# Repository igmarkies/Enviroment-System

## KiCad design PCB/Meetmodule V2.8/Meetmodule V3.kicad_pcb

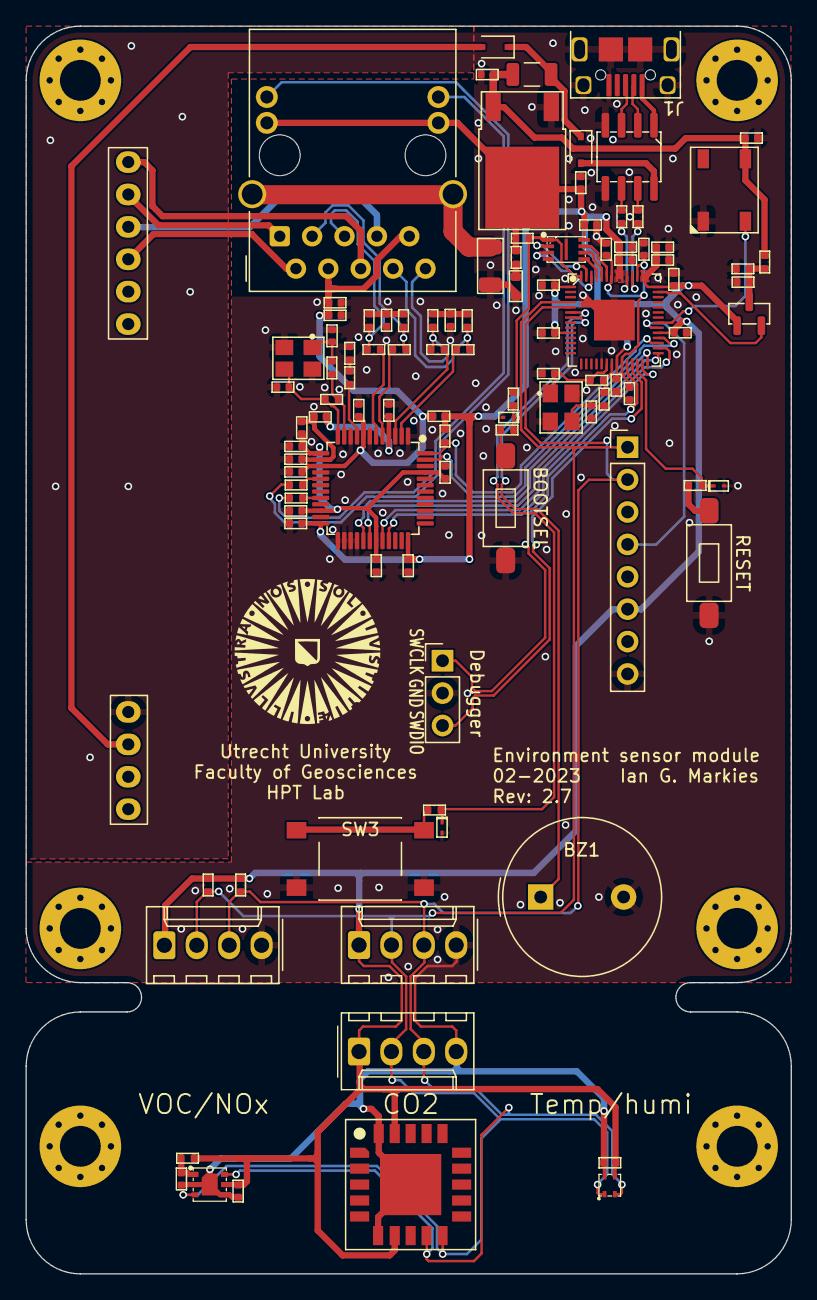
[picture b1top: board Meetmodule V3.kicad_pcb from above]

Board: 2 copper layers, 60.0 x 97.8 mm, 103 parts (0 on the bottom side), 74 nets.

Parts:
BZ1: Buzzer; Buzzer_TDK_PS1240P02BT_D12.2mm_H6.5mm
C1, C2, C3, C4, C5, C6, C7, C8, C9, C15, C18, C19, C20, C21, C22, C23, C25, C26, C27, C28, C29, C30, C32, C36, C39: 0.1uF; Cap 0402_1005Metric
C10, C11: 10uF; Cap 0402_1005Metric
C12, C13, C14, C24, C31, C37, C38: 1uF; Cap 0402_1005Metric
C16, C17: 15pF; Cap 0402_1005Metric
C33: 1nF/2kV; C_1206_3216Metric
C34, C35: 18pF; Cap 0402_1005Metric
D1, D2: BAT60A; D_SOD-323
D3: LED
D4, D6, D7: ESD9B3.3ST5G; D_SOD-923
D5: WS2812B; LED_WS2812B_PLCC4_5.0x5.0mm_P3.2mm
F1: Fuse; Fuse_1206_3216Metric
FB1, FB2, FB3: 120r@100MHz; L_0402_1005Metric
J1: USB_B_Micro; Micro USB, Type B
J2: Ethernet_(100_Base-T_&_PoE); PoE, 10 Pin with LED
J3: Display; PinHeader_1x08_P2.54mm_Vertical
J4: Extra I2C; Molex_KK-254_AE-6410-04A_1x04_P2.54mm_Vertical
J5: Debugger; PinHeader_1x03_P2.54mm_Vertical
J6: Breakout 1; Molex_KK-254_AE-6410-04A_1x04_P2.54mm_Vertical
J7: Breakout 2; Molex_KK-254_AE-6410-04A_1x04_P2.54mm_Vertical
MOD1: Adafruit_3847_connector; Adafruit 3847 connector
Q1: 2N7002; SOT-23
R1, R21, R22: 470R; Res 0402_1005Metric
R2, R3, R8, R10: DNP; Res 0402_1005Metric
R4, R5: 27R; Res 0402_1005Metric
R6: 200k; Res 0402_1005Metric
R7: 100k; Res 0402_1005Metric
R9, R11: 1k; Res 0402_1005Metric
R12: 4k7; Res 0402_1005Metric
R13, R14, R15, R16: 49R9; Res 0402_1005Metric
R17, R18, R19, R20: 3R3; Res 0402_1005Metric
R23: 12K/1%; Res 0402_1005Metric
R24: 300R/1%; Res 0402_1005Metric
R25: 1M; Res 0402_1005Metric
R26: 0R; Res 0402_1005Metric
R27: 4R7; Res 0402_1005Metric
R28, R29, R30: 100R; Res 0402_1005Metric
SW1: BOOTSEL; Switch
SW2: RESET; Switch
SW3: Display; SW_Push_1P1T_NO_6x6mm_H9.5mm
U1: NCP1117-3.3_TO252; TO-252-2
U2: USB6B1; SOIC-8_3.9x4.9mm_P1.27mm
U3: RP2040; QFN-56-1EP_7x7mm_P0.4mm_EP3.2x3.2mm
U4: W25Q16JVUXIQ; SON50P300X200X60-9N
U5: W5100S; LQFP48
U6: SCD4x; SDC4x
U7: SGP41; XDCR_SGP41-D-R4
U8: SHT4x; XDCR_SHT41-AD1B-R2
Y1: 12MHz; Crystal_SMD_Abracon_ABM8G-4Pin_3.2x2.5mm
Y2: 25MHz; Crystal_SMD_Abracon_ABM8G-4Pin_3.2x2.5mm

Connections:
+1V1: C1.1, C2.1, C12.1, U3.23 (DVDD), U3.45 (VREG_VOUT), U3.50 (DVDD)
+1V2A: C23.1, FB2.1, U5.4 (1V2A)
+1V2D: C25.1, C26.1, C27.1, C28.1, FB3.2, U5.13 (1V2D), U5.22 (1V2D), U5.31 (1V2D), U5.45 (1V2D)
+1V2O: C24.1, FB2.2, FB3.1, U5.14 (1V2O)
+3.3V: C3.1, C4.1, C5.1, C6.1, C7.1, C8.1, C9.1, C11.1, C13.1, C14.1, C18.1, C19.1, C20.1, C36.2, C38.1, FB1.1, J2.11 (LEDY-), J2.13 (LEDG-), J3.6, J4.1, J6.1, J7.1, Q1.1 (G), R1.2, R2.2, R3.2, R10.2, R12.1, R27.1, U1.2 (VO), U3.1 (IOVDD), U3.10 (IOVDD), U3.22 (IOVDD), U3.33 (IOVDD), U3.42 (IOVDD), U3.43 (ADC_AVDD), U3.44 (VREG_IN), U3.48 (USB_VDD), U3.49 (IOVDD), U4.8 (VCC), U5.24 (3V3D), U5.36 (3V3D), U6.7 (VDD), U6.19 (VDDH), U7.5 (VDDH), U8.3 (VDD)
+3V3A: C21.1, C22.1, C30.1, C31.1, FB1.2, J2.4 (RCT), J2.9 (TCT), U5.8 (3V3A), U5.15 (3V3A)
+VPoE: D1.2 (A), MOD1.8 (VCC)
+VSYS: C10.1, C39.1, D5.1 (VDD), F1.2, R6.2, U1.3 (VI)
+Vbus: D2.2 (A), U2.8 (VBUS)
/Ethernet W5100S/ACTn: R22.2, U5.20 (ACTn)
/Ethernet W5100S/LNKn: R21.2, U5.17 (LNKn)
/Ethernet W5100S/RX+: R20.2, U5.6 (RXIP)
/Ethernet W5100S/RX-: R19.2, U5.5 (RXIN)
/Ethernet W5100S/RXI+: J2.5 (RD+), R15.2, R20.1
/Ethernet W5100S/RXI-: J2.3 (RD-), R16.2, R19.1
/Ethernet W5100S/TX+: R18.2, U5.3 (TXOP)
/Ethernet W5100S/TX-: R17.2, U5.2 (TXON)
/Ethernet W5100S/TXO+: J2.10 (TD+), R13.2, R18.1
/Ethernet W5100S/TXO-: J2.8 (TD-), R14.2, R17.1
/Ethernet W5100S/VC1+: J2.7 (VC1+), MOD1.3 (VC1+)
/Ethernet W5100S/VC1-: J2.2 (VC1-), MOD1.4 (VC1-)
/Ethernet W5100S/VC2+: J2.6 (VC2+), MOD1.1 (VC2+)
/Ethernet W5100S/VC2-: J2.1 (VC2-), MOD1.2 (VC2-)
/MCU RP2040/Data+: J1.3 (D+), U2.3 (I/O2)
/MCU RP2040/Data-: J1.2 (D-), U2.2 (I/O1)
/MCU RP2040/GPIO29/ADC3: Q1.2 (S), U3.41 (GPIO29_ADC3)
/MCU RP2040/MCU_D+: R4.1, U3.47 (USB_DP)
/MCU RP2040/MCU_D-: R5.1, U3.46 (USB_DM)
/MCU RP2040/QSPI_SCLK: U3.52 (QSPI_SCLK), U4.6 (CLK)
/MCU RP2040/QSPI_SD0: U3.53 (QSPI_SD0), U4.5 (DI_(IO0))
/MCU RP2040/QSPI_SD1: U3.55 (QSPI_SD1), U4.2 (DO_(IO1))
/MCU RP2040/QSPI_SD2: U3.54 (QSPI_SD2), U4.3 (~IO2)
/MCU RP2040/QSPI_SD3: U3.51 (QSPI_SD3), U4.7 (~IO3)
/MCU RP2040/QSPI_SS: R10.1, R11.1, U3.56 (QSPI_SS), U4.1 (~CS)
/MCU RP2040/USB_D+: R4.2, U2.6 (I/O2)
/MCU RP2040/USB_D-: R5.2, U2.7 (I/O1)
BOOTSEL: D4.1 (A1), R11.2, R28.1
GND: BZ1.2 (+), C1.2, C2.2, C3.2, C4.2, C5.2, C6.2, C7.2, C8.2, C9.2, C10.2, C11.2, C12.2, C13.2, C14.2, C15.2, C16.2, C17.2, C18.2, C19.2, C20.2, C21.2, C22.2, C23.2, C24.2, C25.2, C26.2, C27.2, C28.2, C29.2, C30.2, C31.2, C32.2, C33.2, C34.2, C35.2, C36.1, C37.2, C38.2, C39.2, D3.1 (K), D4.2 (A2), D5.3 (VSS), D6.2 (A2), D7.2 (A2), J1.5 (GND), J1.6 (Shield), J3.8, J4.4, J5.2, J6.4, J7.4, MOD1.7 (GND), R7.1, R24.1, SW1.1, SW2.1, SW3.2, U1.1 (GND), U2.4 (GND), U2.5 (GND), U3.19 (TESTEN), U3.57 (GND), U4.4 (GND), U4.9 (EP), U5.1 (GNDA), U5.7 (GNDA), U5.10 (GND), U5.16 (GNDA), U5.23 (GND), U5.25 (MOD0), U5.26 (MOD1), U5.27 (MOD2), U5.28 (MOD3), U5.46 (GND), U6.6 (GND), U6.20 (GND), U6.21 (GND), U7.2 (VSS), U7.4 (n/a), U7.7 (Die_Pad), U8.4 (VSS), Y1.2, Y1.4, Y2.2, Y2.4
GPIO4/Button: D7.1 (A1), R30.2, U3.6 (GPIO4)
GPIO5/Buzzer: BZ1.1 (-), U3.7 (GPIO5)
GPIO22/RST_DIS: J3.4, U3.34 (GPIO22)
GPIO23/LED: D5.4 (DIN), U3.35 (GPIO23)
I2C1_SCL: J3.2, J4.3, J6.3, J7.3, R3.1, U3.5 (GPIO3), U6.9 (SCL), U7.6 (SCL), U8.2 (SCL)
I2C1_SDA: J3.1, J4.2, J6.2, J7.2, R2.1, U3.4 (GPIO2), U6.10 (SDA), U7.3 (SDA), U8.1 (SDA)
INTn: U3.32 (GPIO21), U5.47 (INTn)
unnamed: C15.1, Q1.3 (D), R6.1, R7.2
unnamed: C16.1, R8.2, U3.20 (XIN), Y1.1
unnamed: C17.1, R9.1, Y1.3
unnamed: C29.1, R13.1, R14.1
unnamed: C32.1, R15.1, R16.1
unnamed: C33.1, J2.15 (Shield), J2.16 (Shield)
unnamed: C34.1, R25.2, U5.12 (XSCI), Y2.3
unnamed: C35.1, R26.1, Y2.1
unnamed: C37.1, R27.2, U7.1 (VDD)
unnamed: D1.1 (K), D2.1 (K), F1.1
unnamed: D3.2 (A), R1.1
unnamed: J1.1 (VBUS), U2.1 (VBUS)
unnamed: J2.12 (LEDY+), R21.1
unnamed: J2.14 (LEDG+), R22.1
unnamed: R8.1, R9.2, U3.21 (XOUT)
unnamed: R23.1, R24.2
unnamed: R23.2, U5.9 (RSET_BG)
unnamed: R25.1, R26.2, U5.11 (XSCO)
unnamed: R28.2, SW1.2
unnamed: R29.2, SW2.2
unnamed: R30.1, SW3.1
RSTn: R12.2, U3.31 (GPIO20), U5.48 (RSTn)
RUN: D6.1 (A1), R29.1, U3.26 (RUN)
SPI0_CSn: U3.28 (GPIO17), U5.29 (CSn)
SPI0_RX: U3.27 (GPIO16), U5.33 (MISO)
SPI0_SCK: U3.29 (GPIO18), U5.30 (SCLK)
SPI0_TX: U3.30 (GPIO19), U5.32 (MOSI)
SWCLK: J5.1, U3.24 (SWCLK)
SWDIO: J5.3, U3.25 (SWD)

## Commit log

2023-08-22 Add the codes used for my graduation internship.
2023-08-22 Ordering the files
2023-08-22 Adding the PCB files
2023-08-23 Add created flowcharts
